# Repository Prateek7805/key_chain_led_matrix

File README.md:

# keychain led matrix
This project aims to create a web interface for a custom made PCB for an 8x16 LED matrix display using ESP8266.
The PCB is portable and contains smd components, the project code is written using Embedded C++, HTML, Pure CSS and Vanilla JavaScript with fewer dependencies.

[Demo](https://instagram.com/p/CPmjHNIFKIF/)

### Features: ###
* Pocket size PCB - smaller footprint using 0603 smd LEDs.
* Supports all printable characters in the ASCII table.
* Contains memory (Using SPIFFS).
* Web Interface to display words.
* Totally reprogrammable and hackable.
* Fewer components.
* battery operated and rechargable.
* Web Interface contains additional features to change from STA to AP, deepsleep, reset mcu etc.
* I have also built a webpage to create pixel art (8x8) however I also included the ASCII_Table.h containing all ASCII characters in 8 byte arrays.
* Brightness and scroll speed control.
* fast operation thanks to websockets.
* Uses Wifimanager hence can connect to any AP (Access Point) without reprogramming.

### The PCB is designed in KiCad ###

### Tool to make Pixel Art [click here](https://leddots.000webhostapp.com/)

### Dependencies ###
* [WiFiManager](https://github.com/tzapu/WiFiManager)
* [Websockets](https://github.com/Links2004/arduinoWebSockets)
* [FS Plugin](https://github.com/esp8266/arduino-esp8266fs-plugin/releases)

### Steps to make one: ###

#### Fabricating the PCB ####
* Download and Install KiCad.
* Open the 'keychain.pro' file from '/PCB Design' folder
* Edit the design if needed
* Generate the gerber and drill files
* Upload to the PCB manufacturers website

#### Uploading the code ####
* This requires an FTDI programmer or a nodemcu
* Follow the pinout below and connect the pins accordingly

* Download and Install Arduino IDE  
* Install ESP8266 board  
* [Install the SPIFFS upload plugin](https://randomnerdtutorials.com/install-esp8266-filesystem-uploader-arduino-ide/)  
* Open the keyChainMatrix-v6.ino  
* select the board to be ESP-12 and Flash size as 4MB(FS:2MB)  
* Select the appropriate COM PORT and click upload  
* Click tools > ESP8266 Sketch Data Upload  
* If you are new this I would recommend watching a tutorial on running a blick sketch on ESP8266  

#### Initial Setup ####
* Power on the card sized LED Matrix
* Since it uses WiFiManager WiFi credentials need to be stored in runtime.
* On you PC/smartphone open WiFi settings and connect to 'pocketMatrix' AP.
* It prompts a sign in or manually open a browser and go to '192.168.4.1/'.
* Now scan for the SSID (WiFi Name) or Enter the SSID and Password Manually.
* Now the ESP8266 resets and connect to the provided AP.

### Initial Run ###
* The LED matrix displays the Local IP on reboot or power on. 
* Connect your PC or smartphone to the same AP to which the LED matrix is connected.
* Open a browser and go to the IP address displayed by the LED matrix.
* The page displayed is the interface here
* You can enter any String in the Enter Text Input and click on submit
* The display will instantly display the entered text (Character limit: 1024)
* The range inputs can be used to change the speed and brightness as they fire onInput realtime results can be achived.
* You can rename or delete the strings data box below.
* You can power off the LED display using the On/Off button beside the Delete button however this only powers off the Display and **not the MCU and WiFi**.

### settings ###
* Open the web interface in a browser.
* Click the gear icon on the top right corner of the screen to open settings
* There are a number of cards each of which performs a function 
    * Wifi Mode - Used to change from connect to an AP (STA) to Start an AP (AP)
    * Factory Reset - Click the reset button and click 'Yes' to factory reset the display this will restore the original settings(Warning: The Data will be lost as it clears the SPIFFS)
    * Auto off - Sets an auto off timer
    * WiFi AP - Used to set SSID and Password for the AP mode
    * WiFi Power - clicking PowerDown turns the WIFI radio off However the text will still be displayed, just the wifi will be disabled
    * Reset - Clicking Reset MCU resets the ESP8266.
    * Deepsleep - Puts ESP8266 into deepSleep this can be used if the display needs to be turned off wirelessly however approx 20-50uA current is drawn.

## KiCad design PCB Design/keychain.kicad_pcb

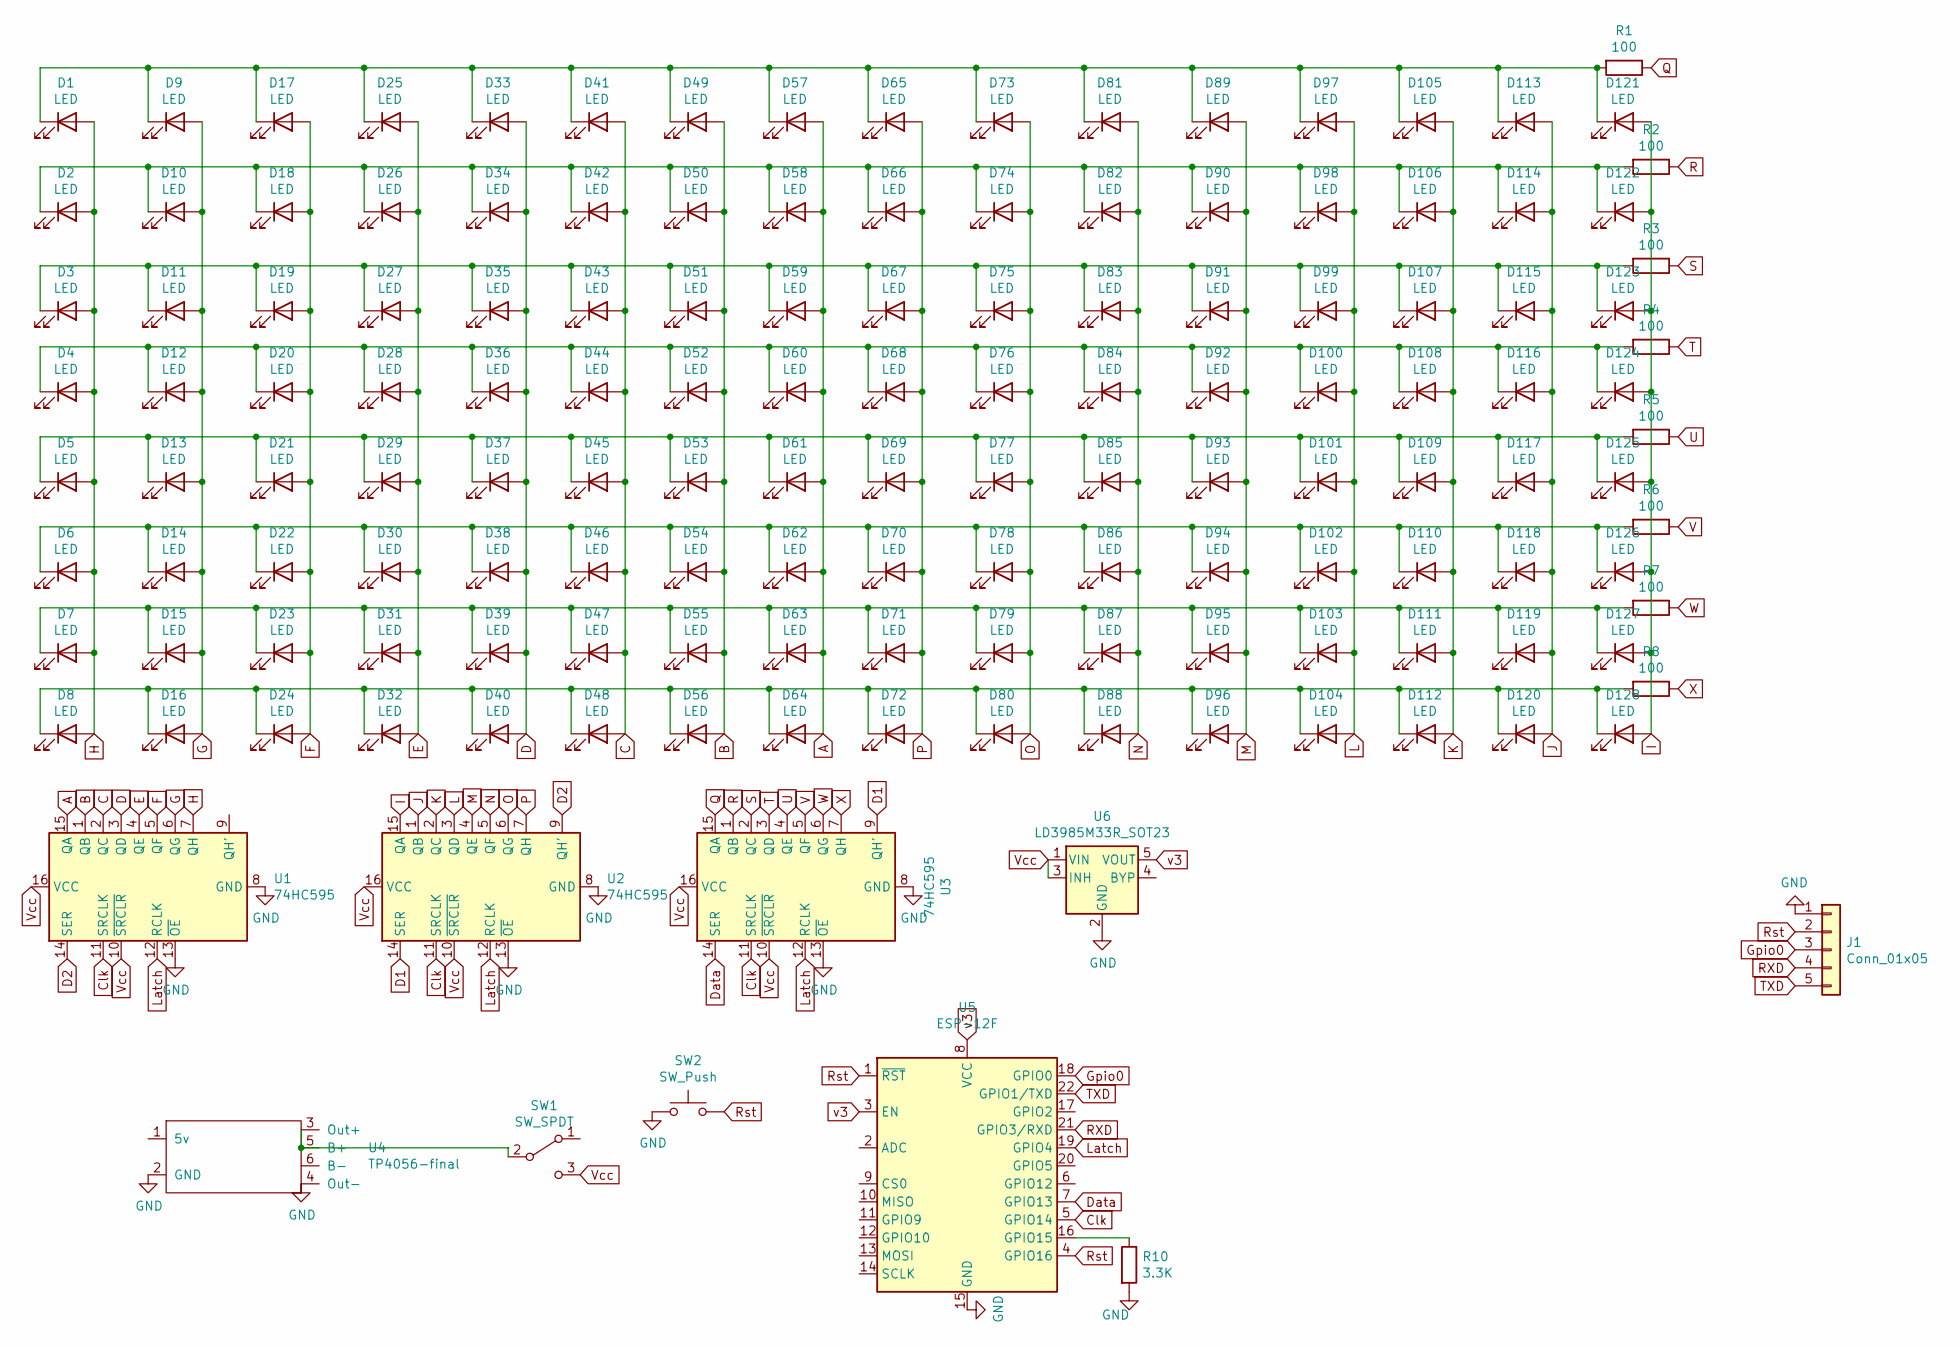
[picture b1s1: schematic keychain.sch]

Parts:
D1, D2, D3, D4, D5, D6, D7, D8, D9, D10, D11, D12, D13, D14, D15, D16, D17, D18, D19, D20, D21, D22, D23, D24, D25, D26, D27, D28, D29, D30, D31, D32, D33, D34, D35, D36, D37, D38, D39, D40, D41, D42, D43, D44, D45, D46, D47, D48, D49, D50, D51, D52, D53, D54, D55, D56, D57, D58, D59, D60, D61, D62, D63, D64, D65, D66, D67, D68, D69, D70, D71, D72, D73, D74, D75, D76, D77, D78, D79, D80, D81, D82, D83, D84, D85, D86, D87, D88, D89, D90, D91, D92, D93, D94, D95, D96, D97, D98, D99, D100, D101, D102, D103, D104, D105, D106, D107, D108, D109, D110, D111, D112, D113, D114, D115, D116, D117, D118, D119, D120, D121, D122, D123, D124, D125, D126, D127, D128: LED; LED_0603_1608Metric
J1: Conn_01x05; PinSocket_1x05_P2.54mm_Vertical
R1, R2, R3, R4, R5, R6, R7, R8: 100; R_0603_1608Metric_Pad1.05x0.95mm_HandSolder
R10: 3.3K; R_0603_1608Metric_Pad1.05x0.95mm_HandSolder
SW1: SW_SPDT; SW_SPDT_PCM12
SW2: SW_Push; SW_SPST_CK_RS282G05A3
U1, U2, U3: 74HC595; SOIC-16_3.9x9.9mm_P1.27mm
U4: TP4056-final; TP4056-18650
U5: ESP-12F; ESP-12E
U6: LD3985M33R_SOT23; SOT-23-5

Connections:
A: D57.2 (A), D58.2 (A), D59.2 (A), D60.2 (A), D61.2 (A), D62.2 (A), D63.2 (A), D64.2 (A), U1.15 (QA)
B: D49.2 (A), D50.2 (A), D51.2 (A), D52.2 (A), D53.2 (A), D54.2 (A), D55.2 (A), D56.2 (A), U1.1 (QB)
C: D41.2 (A), D42.2 (A), D43.2 (A), D44.2 (A), D45.2 (A), D46.2 (A), D47.2 (A), D48.2 (A), U1.2 (QC)
Clk: U1.11 (SRCLK), U2.11 (SRCLK), U3.11 (SRCLK), U5.5 (GPIO14)
D: D33.2 (A), D34.2 (A), D35.2 (A), D36.2 (A), D37.2 (A), D38.2 (A), D39.2 (A), D40.2 (A), U1.3 (QD)
D1: U2.14 (SER), U3.9 (QH')
D2: U1.14 (SER), U2.9 (QH')
Data: U3.14 (SER), U5.7 (GPIO13)
E: D25.2 (A), D26.2 (A), D27.2 (A), D28.2 (A), D29.2 (A), D30.2 (A), D31.2 (A), D32.2 (A), U1.4 (QE)
F: D17.2 (A), D18.2 (A), D19.2 (A), D20.2 (A), D21.2 (A), D22.2 (A), D23.2 (A), D24.2 (A), U1.5 (QF)
G: D9.2 (A), D10.2 (A), D11.2 (A), D12.2 (A), D13.2 (A), D14.2 (A), D15.2 (A), D16.2 (A), U1.6 (QG)
GND: J1.1, R10.2, SW2.1, U1.8 (GND), U1.13 (~OE), U2.8 (GND), U2.13 (~OE), U3.8 (GND), U3.13 (~OE), U4.2 (GND), U4.4 (Out-), U5.15 (GND), U6.2 (GND)
Gpio0: J1.3, U5.18 (GPIO0)
H: D1.2 (A), D2.2 (A), D3.2 (A), D4.2 (A), D5.2 (A), D6.2 (A), D7.2 (A), D8.2 (A), U1.7 (QH)
I: D121.2 (A), D122.2 (A), D123.2 (A), D124.2 (A), D125.2 (A), D126.2 (A), D127.2 (A), D128.2 (A), U2.15 (QA)
J: D113.2 (A), D114.2 (A), D115.2 (A), D116.2 (A), D117.2 (A), D118.2 (A), D119.2 (A), D120.2 (A), U2.1 (QB)
K: D105.2 (A), D106.2 (A), D107.2 (A), D108.2 (A), D109.2 (A), D110.2 (A), D111.2 (A), D112.2 (A), U2.2 (QC)
L: D97.2 (A), D98.2 (A), D99.2 (A), D100.2 (A), D101.2 (A), D102.2 (A), D103.2 (A), D104.2 (A), U2.3 (QD)
Latch: U1.12 (RCLK), U2.12 (RCLK), U3.12 (RCLK), U5.19 (GPIO4)
M: D89.2 (A), D90.2 (A), D91.2 (A), D92.2 (A), D93.2 (A), D94.2 (A), D95.2 (A), D96.2 (A), U2.4 (QE)
N: D81.2 (A), D82.2 (A), D83.2 (A), D84.2 (A), D85.2 (A), D86.2 (A), D87.2 (A), D88.2 (A), U2.5 (QF)
unnamed: D1.1 (K), D9.1 (K), D17.1 (K), D25.1 (K), D33.1 (K), D41.1 (K), D49.1 (K), D57.1 (K), D65.1 (K), D73.1 (K), D81.1 (K), D89.1 (K), D97.1 (K), D105.1 (K), D113.1 (K), D121.1 (K), R1.2
unnamed: D2.1 (K), D10.1 (K), D18.1 (K), D26.1 (K), D34.1 (K), D42.1 (K), D50.1 (K), D58.1 (K), D66.1 (K), D74.1 (K), D82.1 (K), D90.1 (K), D98.1 (K), D106.1 (K), D114.1 (K), D122.1 (K), R2.2
unnamed: D4.1 (K), D12.1 (K), D20.1 (K), D28.1 (K), D36.1 (K), D44.1 (K), D52.1 (K), D60.1 (K), D68.1 (K), D76.1 (K), D84.1 (K), D92.1 (K), D100.1 (K), D108.1 (K), D116.1 (K), D124.1 (K), R4.2
unnamed: D5.1 (K), D13.1 (K), D21.1 (K), D29.1 (K), D37.1 (K), D45.1 (K), D53.1 (K), D61.1 (K), D69.1 (K), D77.1 (K), D85.1 (K), D93.1 (K), D101.1 (K), D109.1 (K), D117.1 (K), D125.1 (K), R5.2
unnamed: D6.1 (K), D14.1 (K), D22.1 (K), D30.1 (K), D38.1 (K), D46.1 (K), D54.1 (K), D62.1 (K), D70.1 (K), D78.1 (K), D86.1 (K), D94.1 (K), D102.1 (K), D110.1 (K), D118.1 (K), D126.1 (K), R6.2
unnamed: D7.1 (K), D15.1 (K), D23.1 (K), D31.1 (K), D39.1 (K), D47.1 (K), D55.1 (K), D63.1 (K), D71.1 (K), D79.1 (K), D87.1 (K), D95.1 (K), D103.1 (K), D111.1 (K), D119.1 (K), D127.1 (K), R7.2
unnamed: D8.1 (K), D16.1 (K), D24.1 (K), D32.1 (K), D40.1 (K), D48.1 (K), D56.1 (K), D64.1 (K), D72.1 (K), D80.1 (K), D88.1 (K), D96.1 (K), D104.1 (K), D112.1 (K), D120.1 (K), D128.1 (K), R8.2
unnamed: D3.1 (K), D11.1 (K), D19.1 (K), D27.1 (K), D35.1 (K), D43.1 (K), D51.1 (K), D59.1 (K), D67.1 (K), D75.1 (K), D83.1 (K), D91.1 (K), D99.1 (K), D107.1 (K), D115.1 (K), D123.1 (K), R3.2
unnamed: R10.1, U5.16 (GPIO15)
unnamed: SW1.2 (B), U4.3 (Out+), U4.5 (B+)
O: D73.2 (A), D74.2 (A), D75.2 (A), D76.2 (A), D77.2 (A), D78.2 (A), D79.2 (A), D80.2 (A), U2.6 (QG)
P: D65.2 (A), D66.2 (A), D67.2 (A), D68.2 (A), D69.2 (A), D70.2 (A), D71.2 (A), D72.2 (A), U2.7 (QH)
Q: R1.1, U3.15 (QA)
R: R2.1, U3.1 (QB)
RXD: J1.4, U5.21 (GPIO3/RXD)
Rst: J1.2, SW2.2, U5.1 (~RST), U5.4 (GPIO16)
S: R3.1, U3.2 (QC)
T: R4.1, U3.3 (QD)
TXD: J1.5, U5.22 (GPIO1/TXD)
U: R5.1, U3.4 (QE)
V: R6.1, U3.5 (QF)
Vcc: SW1.3 (C), U1.10 (~SRCLR), U1.16 (VCC), U2.10 (~SRCLR), U2.16 (VCC), U3.10 (~SRCLR), U3.16 (VCC), U6.1 (VIN), U6.3 (INH)
W: R7.1, U3.6 (QG)
X: R8.1, U3.7 (QH)
v3: U5.3 (EN), U5.8 (VCC), U6.5 (VOUT)

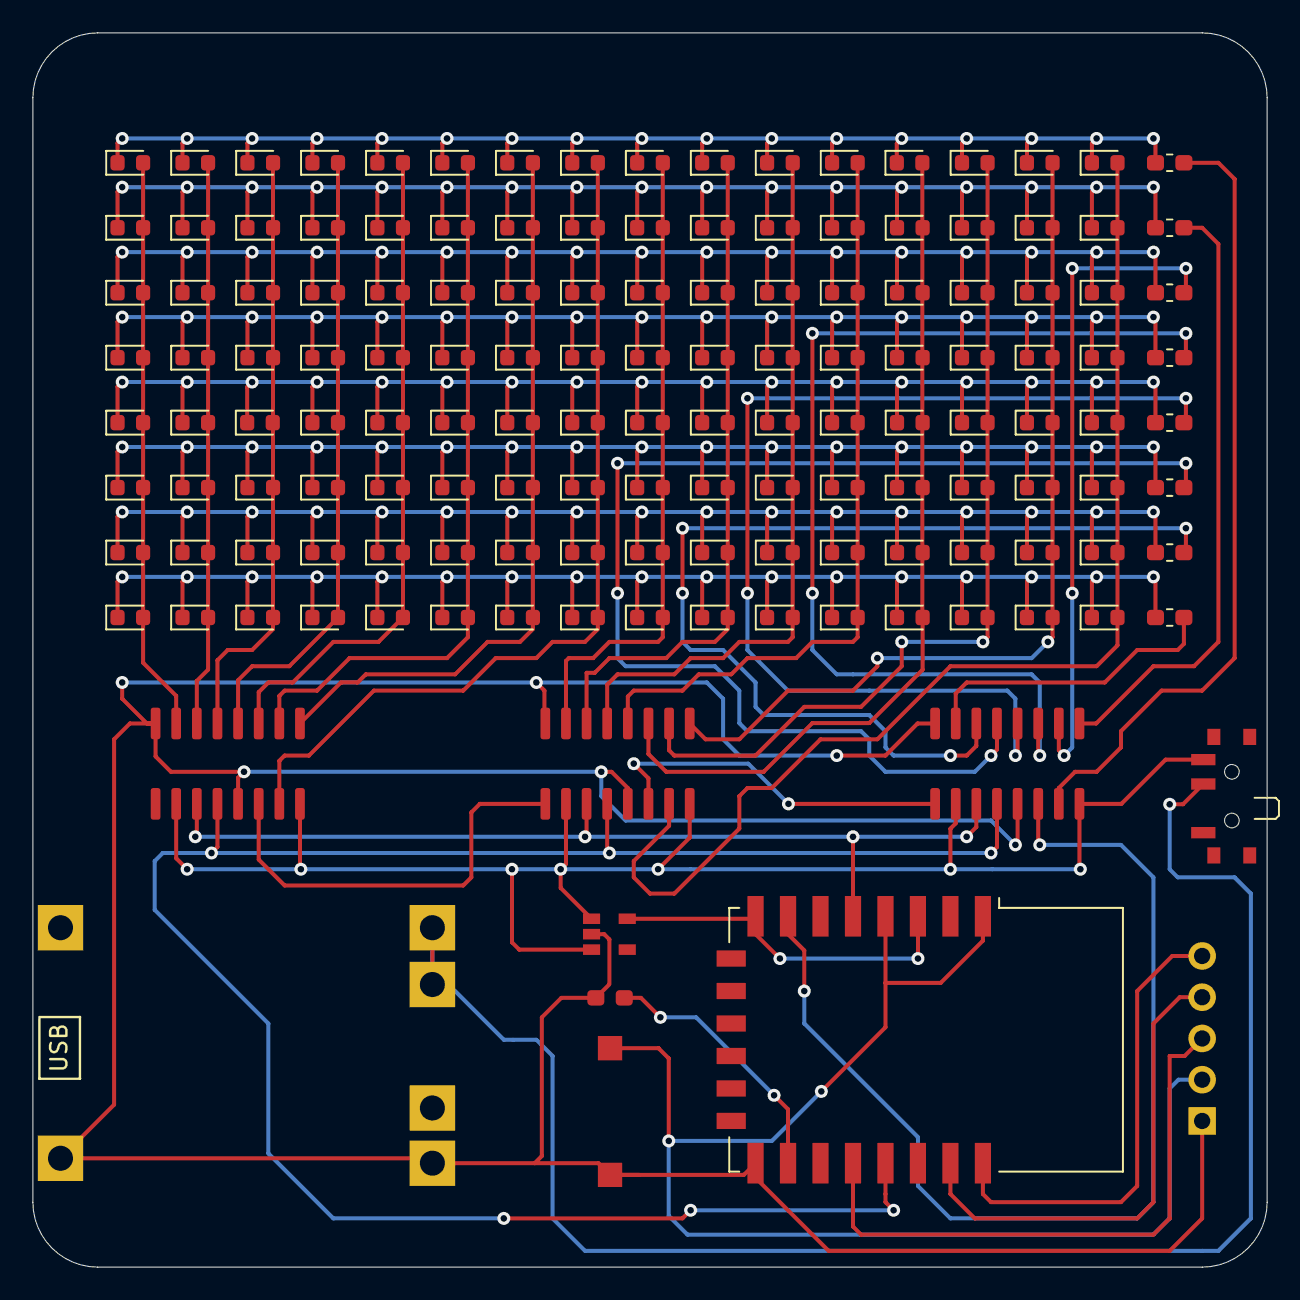
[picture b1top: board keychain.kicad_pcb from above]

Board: 2 copper layers, 76.0 x 76.0 mm, 146 parts (0 on the bottom side), 46 nets.

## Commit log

2021-11-03 SPIFFS data
2021-11-03 Added SPIFFS Files
2021-11-03 Create test
2021-11-03 Added KiCad files
2021-11-03 Added Gerbers
2021-11-03 Added 3D model
2021-11-03 Added Pinout
